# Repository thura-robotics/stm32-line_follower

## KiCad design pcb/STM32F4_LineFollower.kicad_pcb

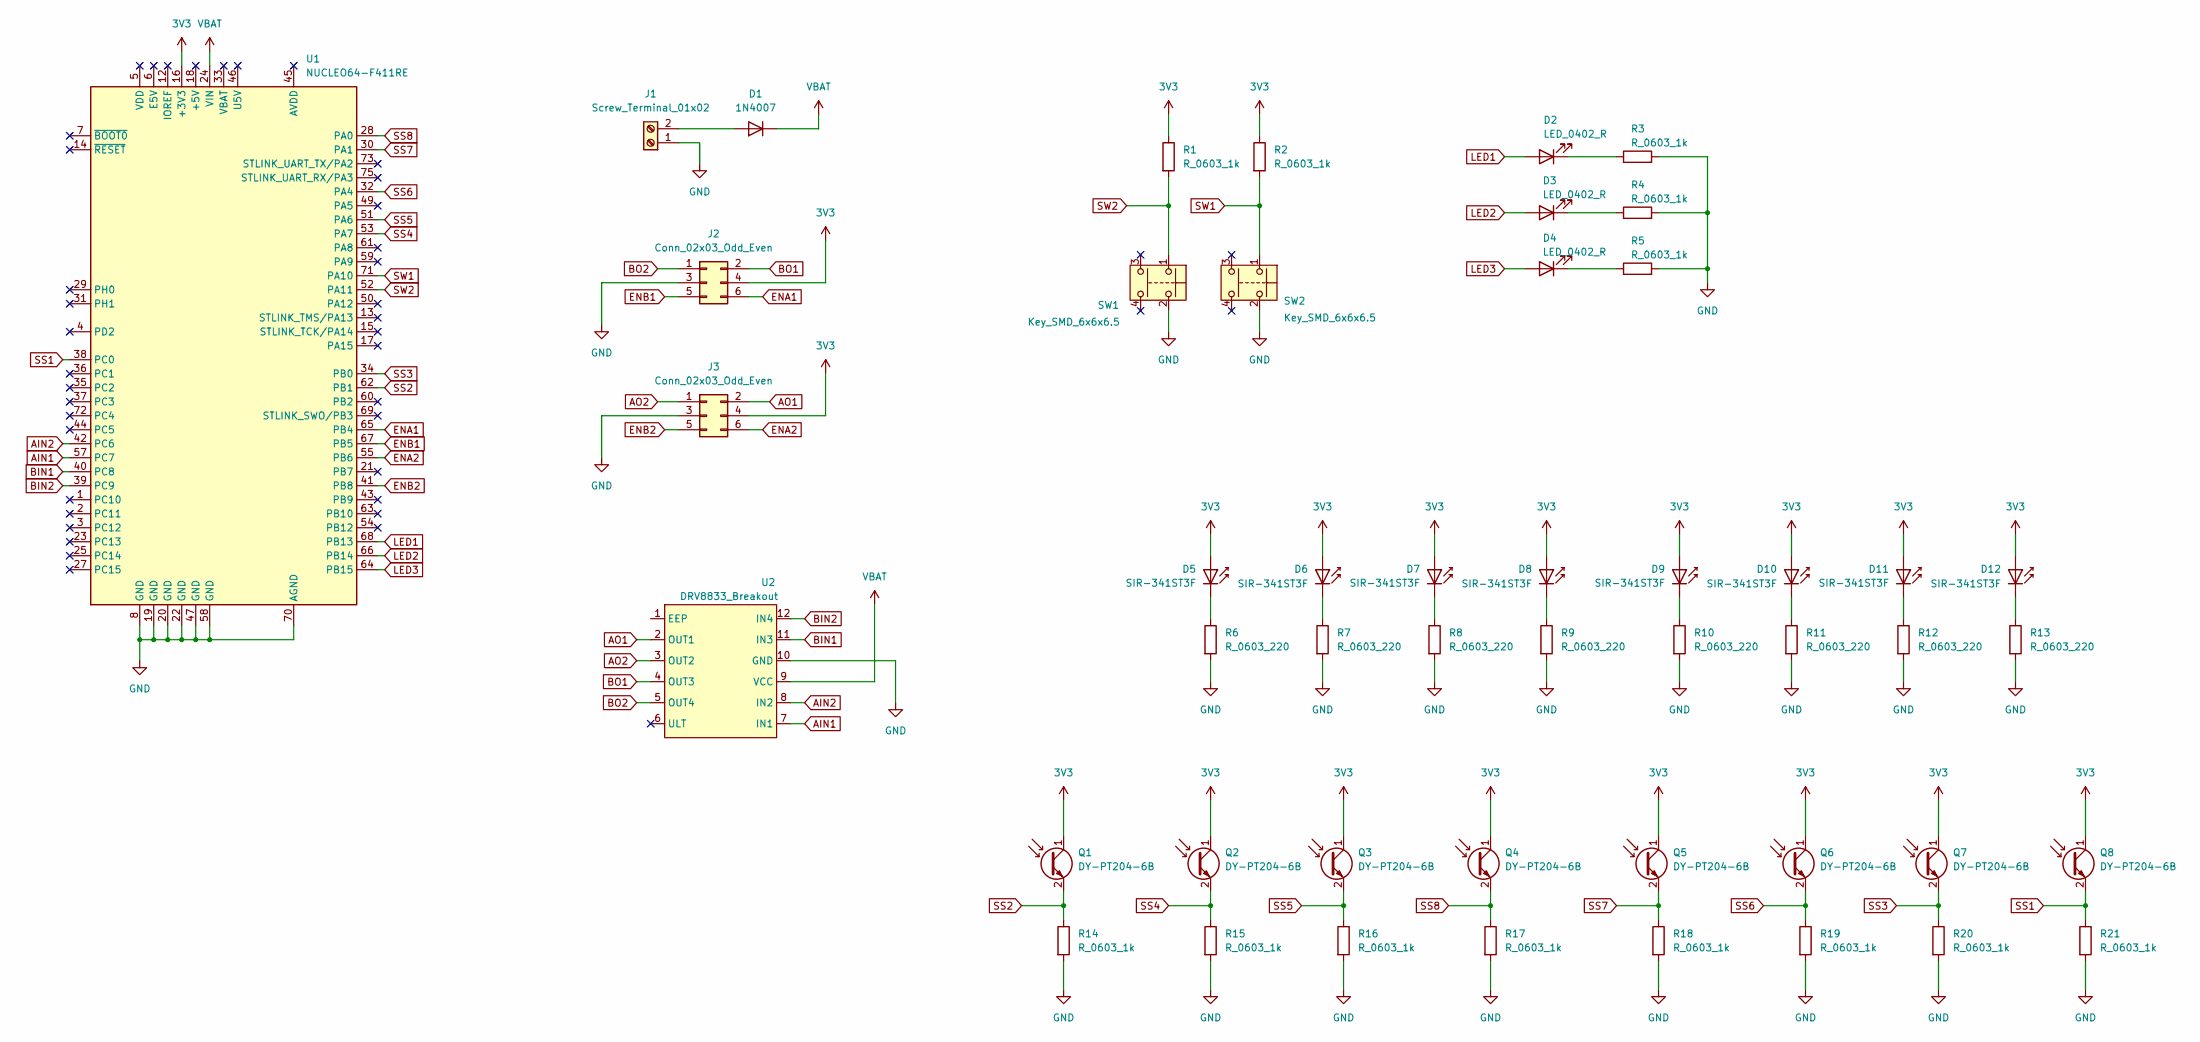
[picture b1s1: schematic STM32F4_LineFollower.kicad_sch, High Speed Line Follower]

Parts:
D1: 1N4007; D_DO-41_SOD81_P10.16mm_Horizontal
D2, D3, D4: LED_0402_R; LED_0402_1005Metric_Pad0.77x0.64mm_HandSolder
D5, D6, D7, D8, D9, D10, D11, D12: SIR-341ST3F; LED_D3.0mm_Clear
J1: Screw_Terminal_01x02; TerminalBlock_4Ucon_1x02_P3.50mm_Horizontal
J2, J3: Conn_02x03_Odd_Even; PinHeader_2x03_P2.54mm_Vertical
Q1, Q2, Q3, Q4, Q5, Q6, Q7, Q8: DY-PT204-6B; LED_D3.0mm_IRBlack
R1, R2, R3, R4, R5, R14, R15, R16, R17, R18, R19, R20, R21: R_0603_1k; R_0603_1608Metric_Pad0.98x0.95mm_HandSolder
R6, R7, R8, R9, R10, R11, R12, R13: R_0603_220; R_0603_1608Metric_Pad0.98x0.95mm_HandSolder
SW1, SW2: Key_SMD_6x6x6.5; SW_Push_1P1T_NO_E-Switch_TL3301NxxxxxG_v2
U1: NUCLEO64-F411RE; BOARD_NUCLEO-F411RE
U2: DRV8833_Breakout

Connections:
3V3: D5.2 (A), D6.2 (A), D7.2 (A), D8.2 (A), D9.2 (A), D10.2 (A), D11.2 (A), D12.2 (A), J2.4, J3.4, Q1.1 (C), Q2.1 (C), Q3.1 (C), Q4.1 (C), Q5.1 (C), Q6.1 (C), Q7.1 (C), Q8.1 (C), R1.1, R2.1, U1.16 (+3V3)
AIN1: U1.57 (PC7), U2.7 (IN1)
AIN2: U1.42 (PC6), U2.8 (IN2)
AO1: J3.2, U2.2 (OUT1)
AO2: J3.1, U2.3 (OUT2)
BIN1: U1.40 (PC8), U2.11 (IN3)
BIN2: U1.39 (PC9), U2.12 (IN4)
BO1: J2.2, U2.4 (OUT3)
BO2: J2.1, U2.5 (OUT4)
ENA1: J2.6, U1.65 (PB4)
ENA2: J3.6, U1.55 (PB6)
ENB1: J2.5, U1.67 (PB5)
ENB2: J3.5, U1.41 (PB8)
GND: J1.1, J2.3, J3.3, R3.2, R4.2, R5.2, R6.2, R7.2, R8.2, R9.2, R10.2, R11.2, R12.2, R13.2, R14.2, R15.2, R16.2, R17.2, R18.2, R19.2, R20.2, R21.2, SW1.2, SW2.2, U1.8 (GND), U1.19 (GND), U1.20 (GND), U1.22 (GND), U1.47 (GND), U1.58 (GND), U1.70 (AGND), U2.10 (GND)
LED1: D2.2 (A), U1.68 (PB13)
LED2: D3.2 (A), U1.66 (PB14)
LED3: D4.2 (A), U1.64 (PB15)
unnamed: D1.2 (A), J1.2
unnamed: D2.1 (K), R3.1
unnamed: D3.1 (K), R4.1
unnamed: D4.1 (K), R5.1
unnamed: D5.1 (K), R6.1
unnamed: D6.1 (K), R7.1
unnamed: D7.1 (K), R8.1
unnamed: D8.1 (K), R9.1
unnamed: D9.1 (K), R10.1
unnamed: D10.1 (K), R11.1
unnamed: D11.1 (K), R12.1
unnamed: D12.1 (K), R13.1
SS1: Q8.2 (E), R21.1, U1.38 (PC0)
SS2: Q1.2 (E), R14.1, U1.62 (PB1)
SS3: Q7.2 (E), R20.1, U1.34 (PB0)
SS4: Q2.2 (E), R15.1, U1.53 (PA7)
SS5: Q3.2 (E), R16.1, U1.51 (PA6)
SS6: Q6.2 (E), R19.1, U1.32 (PA4)
SS7: Q5.2 (E), R18.1, U1.30 (PA1)
SS8: Q4.2 (E), R17.1, U1.28 (PA0)
SW1: R2.2, SW2.1, U1.71 (PA10)
SW2: R1.2, SW1.1, U1.52 (PA11)
VBAT: D1.1 (K), U1.24 (VIN), U2.9 (VCC)

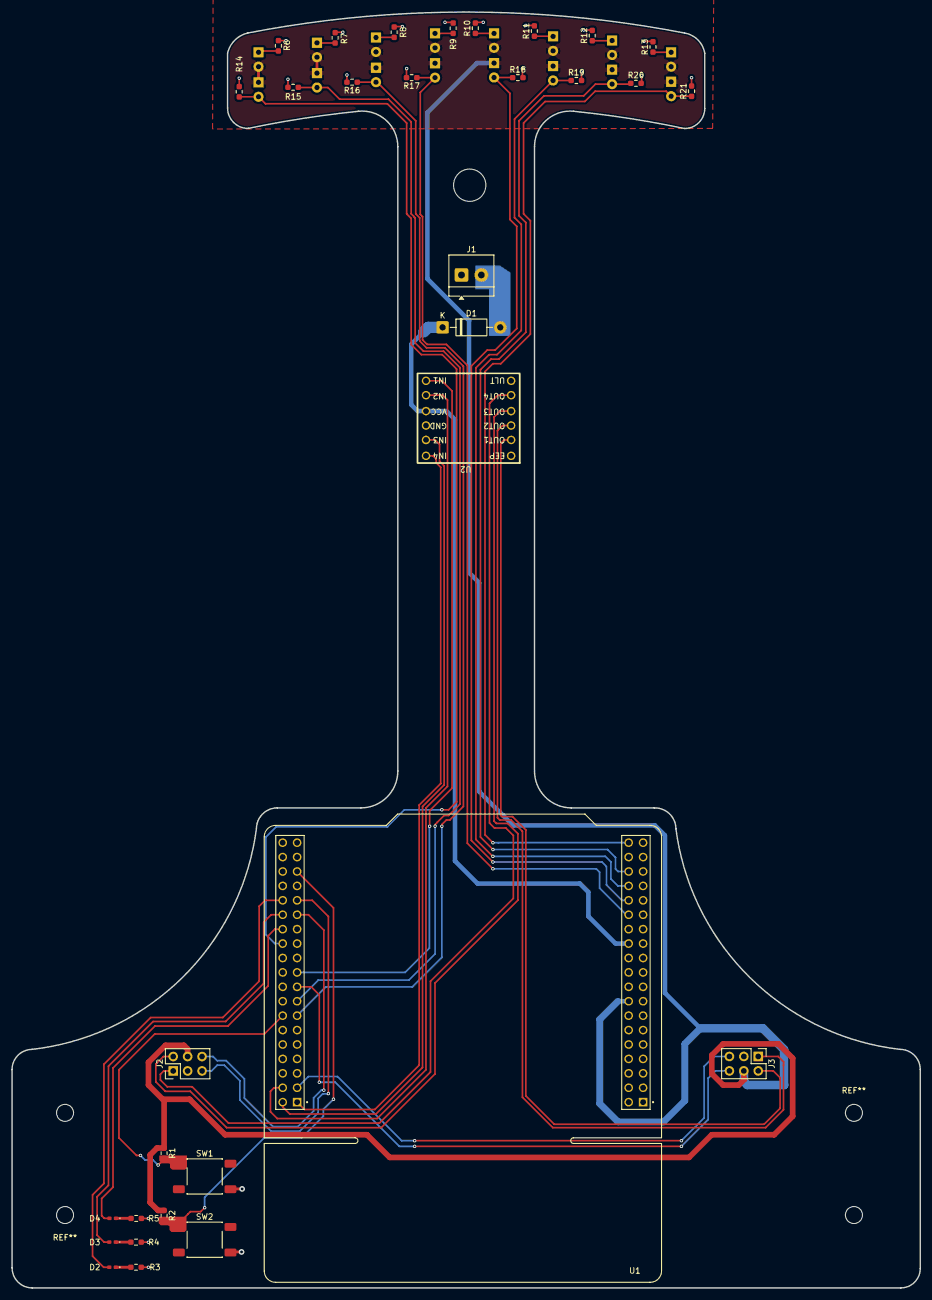
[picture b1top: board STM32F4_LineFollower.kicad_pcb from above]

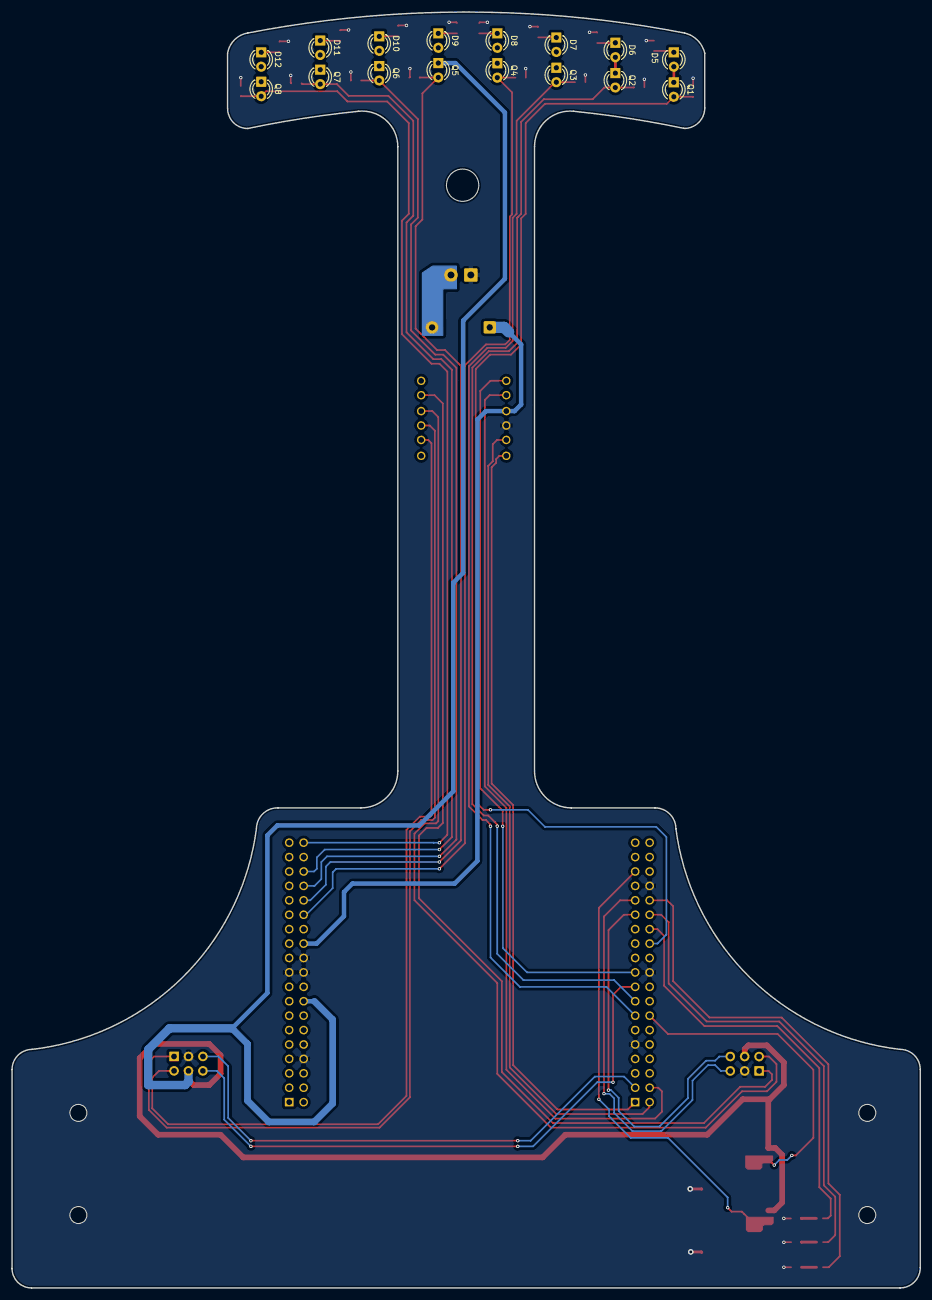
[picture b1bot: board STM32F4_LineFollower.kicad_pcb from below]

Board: 2 copper layers, 160.0 x 224.8 mm, 48 parts (16 on the bottom side), 40 nets.

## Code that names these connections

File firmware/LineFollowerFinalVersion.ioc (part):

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Mcu.Name=STM32F411R(C-E)Tx
Mcu.Package=LQFP64
Mcu.UserName=STM32F411RETx
PA0-WKUP.Signal=ADCx_IN0
PA1.Signal=ADCx_IN1
PA10.GPIOParameters=GPIO_Label
PA10.GPIO_Label=Right Switch
PA10.Signal=GPIO_Input
PA11.GPIOParameters=GPIO_Label
PA11.GPIO_Label=Left Switch
PA11.Signal=GPIO_Input
PA2.Mode=Asynchronous
PA2.Signal=USART2_TX
PA3.Mode=Asynchronous
PA3.Signal=USART2_RX
PA4.Signal=ADCx_IN4
PA5.GPIOParameters=GPIO_Label
PA5.GPIO_Label=LED ON STM
PA5.Signal=GPIO_Output
PA6.Signal=ADCx_IN6
PA7.Signal=ADCx_IN7
PB0.Signal=ADCx_IN8
PB1.Signal=ADCx_IN9
PB13.Signal=GPIO_Output
PB14.Signal=GPIO_Output
PB15.Signal=GPIO_Output
PB4.GPIOParameters=GPIO_Label
PB4.GPIO_Label=ENA1
PB4.Signal=GPIO_Input
PB5.GPIOParameters=GPIO_Label
PB5.GPIO_Label=ENB1
PB5.Signal=GPIO_Input
PB6.GPIOParameters=GPIO_Label
PB6.GPIO_Label=ENA2
PB6.Signal=GPIO_Input
PB8.GPIOParameters=GPIO_Label
PB8.GPIO_Label=ENB2
PB8.Signal=GPIO_Input
PC0.Signal=ADCx_IN10
PC1.Signal=ADCx_IN11
PC13-ANTI_TAMP.GPIOParameters=GPIO_Label
PC13-ANTI_TAMP.GPIO_Label=Blue Button
PC13-ANTI_TAMP.Signal=GPIO_Input
PC2.Signal=ADCx_IN12
PC6.GPIOParameters=GPIO_Label
PC6.GPIO_Label=TIM3_CH1(PC6)_L
PC6.Signal=S_TIM3_CH1
PC7.GPIOParameters=GPIO_Label
PC7.GPIO_Label=L_TIM3_CH2
PC7.Signal=S_TIM3_CH2
PC8.GPIOParameters=GPIO_Label
PC8.GPIO_Label=TIM3_CH3(PC8)_R
PC8.Signal=S_TIM3_CH3
PC9.GPIOParameters=GPIO_Label
PC9.GPIO_Label=R_TIM3_CH4
PC9.Signal=S_TIM3_CH4
RCC.HSE_VALUE=25000000
RCC.SYSCLKFreq_VALUE=80000000
RCC.SYSCLKSource=RCC_SYSCLKSOURCE_PLLCLK
board=custom

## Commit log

2026-05-17 Rearrange the file structure
2026-05-17 removed .json
2026-05-17 removed .json completely
2026-05-17 Added 3D model
2026-05-20 Added step file
2026-05-20 Add GLB file
2026-05-20 Fixed GLB
